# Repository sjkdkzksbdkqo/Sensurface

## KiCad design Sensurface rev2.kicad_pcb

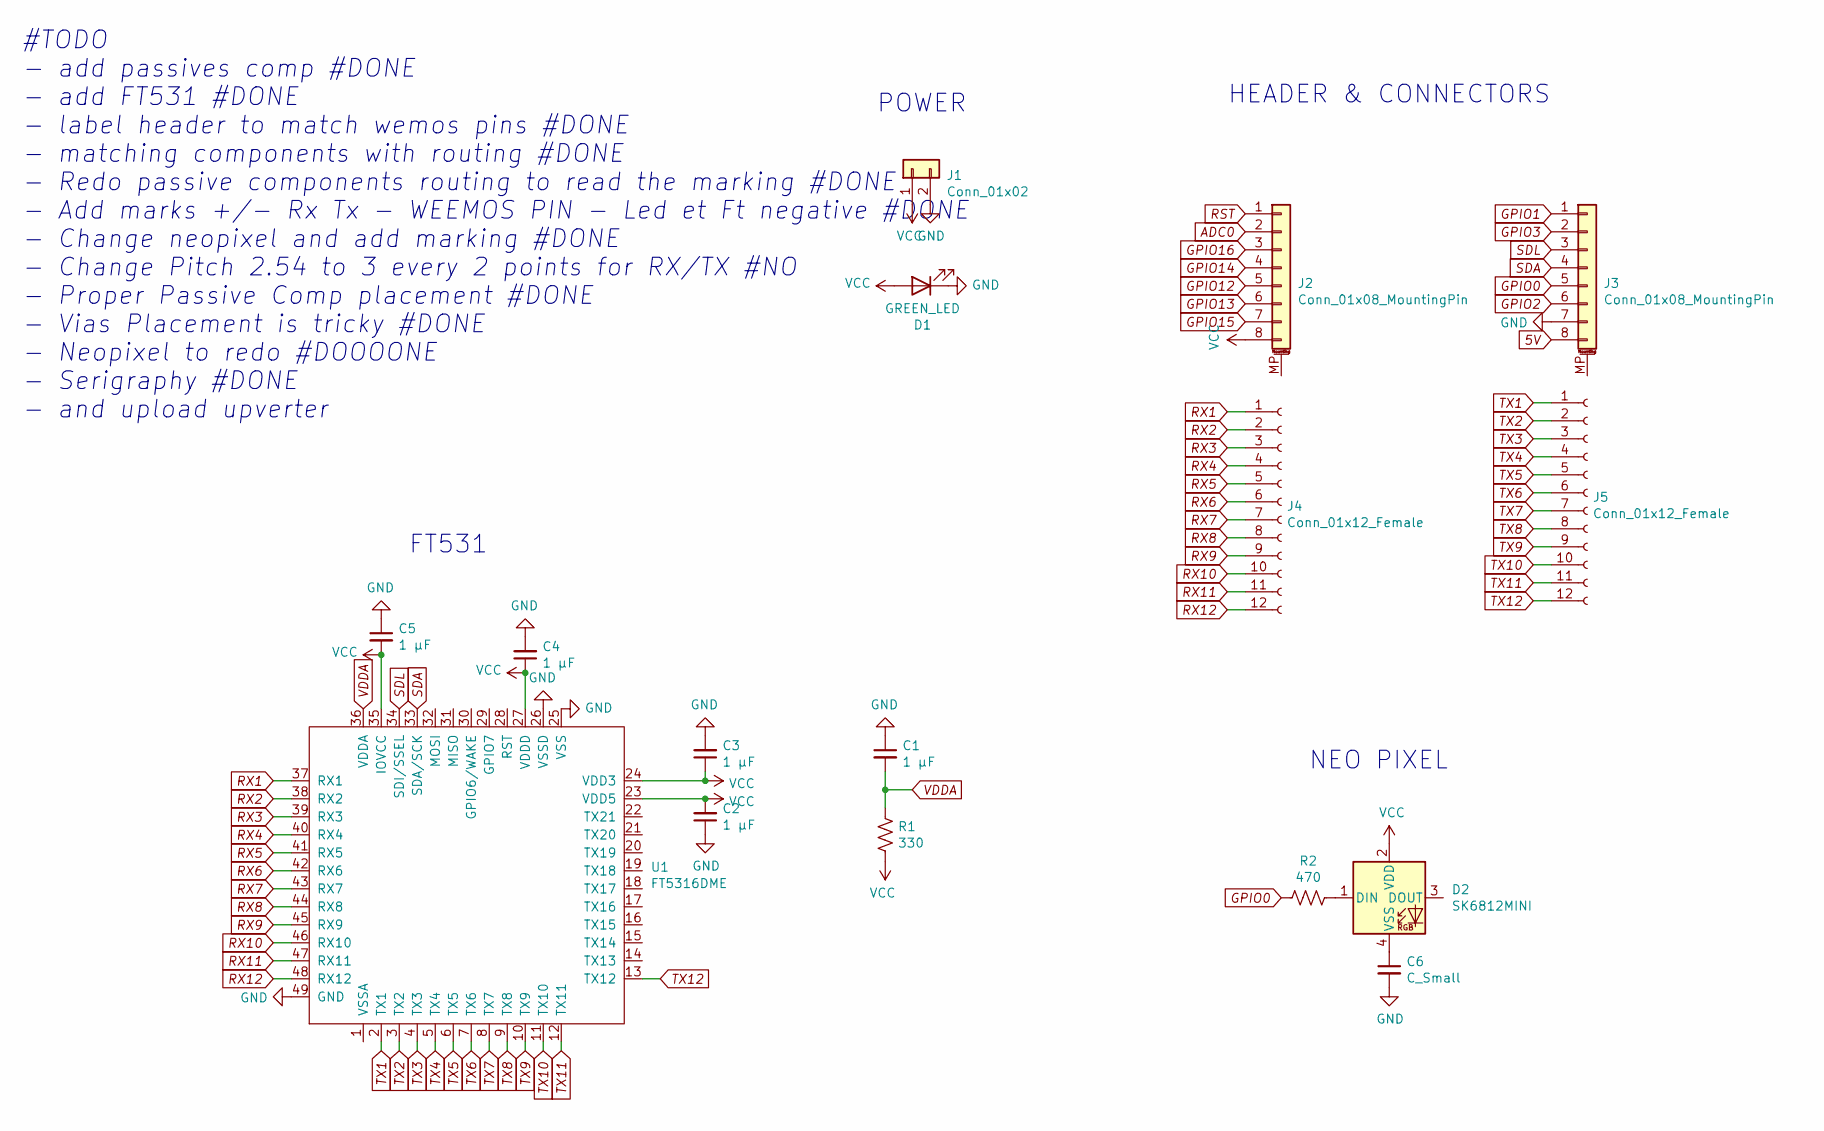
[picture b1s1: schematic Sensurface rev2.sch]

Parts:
C1, C2, C3, C4, C5: 1 µF; C_0603_1608Metric
C6: C_Small; C_0603_1608Metric
D1: GREEN_LED; LED_0805_2012Metric
D2: SK6812MINI; LED_SK6812MINI_PLCC4_3.5x3.5mm_P1.75mm
J1: Conn_01x02; JST_EH_S2B-EH_1x02_P2.50mm_Horizontal
J2, J3: Conn_01x08_MountingPin; PinHeader_1x08_P2.54mm_Vertical
J4, J5: Conn_01x12_Female; TerminalBlock_Phoenix_MPT-0,5-12-2.54_1x12_P2.54mm_Horizont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
R1: 330; R_0603_1608Metric
R2: 470; R_0603_1608Metric
U1: FT5316DME; QFN-48-1EP_6x6mm_P0.4mm_EP4.2x4.2mm

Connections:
5V: J3.8
ADC0: J2.2
GND: C1.1, C2.1, C3.2, C4.2, C5.1, C6.2, D1.1 (K), J1.2, J3.7, U1.25 (VSS), U1.26 (VSSD), U1.49 (GND)
GPIO0: J3.5, R2.2
GPIO1: J3.1
GPIO2: J3.6
GPIO3: J3.2
GPIO12: J2.5
GPIO13: J2.6
GPIO14: J2.4
GPIO15: J2.7
GPIO16: J2.3
unnamed: C6.1, D2.4 (VSS)
unnamed: D2.1 (DIN), R2.1
RST: J2.1
RX1: J4.1, U1.37 (RX1)
RX2: J4.2, U1.38 (RX2)
RX3: J4.3, U1.39 (RX3)
RX4: J4.4, U1.40 (RX4)
RX5: J4.5, U1.41 (RX5)
RX6: J4.6, U1.42 (RX6)
RX7: J4.7, U1.43 (RX7)
RX8: J4.8, U1.44 (RX8)
RX9: J4.9, U1.45 (RX9)
RX10: J4.10, U1.46 (RX10)
RX11: J4.11, U1.47 (RX11)
RX12: J4.12, U1.48 (RX12)
SDA: J3.4, U1.33 (SDA/SCK)
SDL: J3.3, U1.34 (SDI/SSEL)
TX1: J5.1, U1.2 (TX1)
TX2: J5.2, U1.3 (TX2)
TX3: J5.3, U1.4 (TX3)
TX4: J5.4, U1.5 (TX4)
TX5: J5.5, U1.6 (TX5)
TX6: J5.6, U1.7 (TX6)
TX7: J5.7, U1.8 (TX7)
TX8: J5.8, U1.9 (TX8)
TX9: J5.9, U1.10 (TX9)
TX10: J5.10, U1.11 (TX10)
TX11: J5.11, U1.12 (TX11)
TX12: J5.12, U1.13 (TX12)
VCC: C2.2, C3.1, C4.1, C5.2, D1.2 (A), D2.2 (VDD), J1.1, J2.8, R1.2, U1.23 (VDD5), U1.24 (VDD3), U1.27 (VDDD), U1.35 (IOVCC)
VDDA: C1.2, R1.1, U1.36 (VDDA)

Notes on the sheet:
FT531
POWER
HEADER & CONNECTORS
NEO PIXEL
#TODO - add passives comp #DONE - add FT531 #DONE - label header to match wemos pins #DONE - matching components with routing #DONE - Redo passive components routing to read the marking #DONE - Add marks +/- Rx Tx - WEEMOS PIN - Led et Ft negative #DONE - Change neopixel and add marking #DONE - Cha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

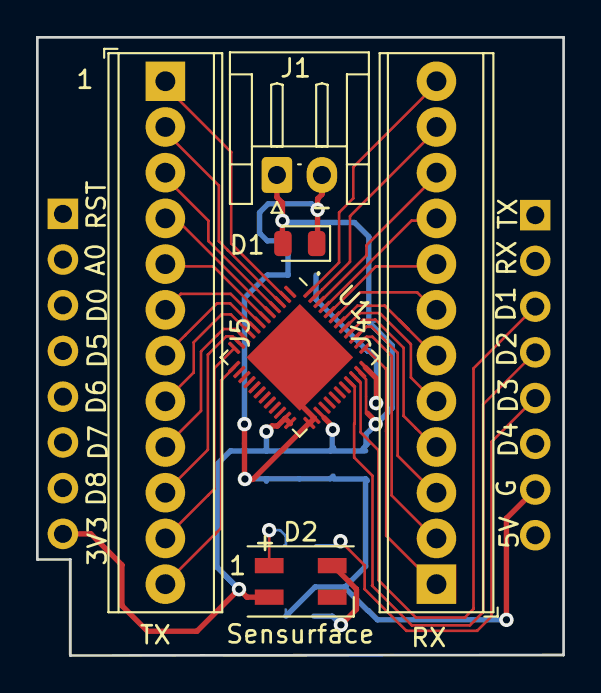
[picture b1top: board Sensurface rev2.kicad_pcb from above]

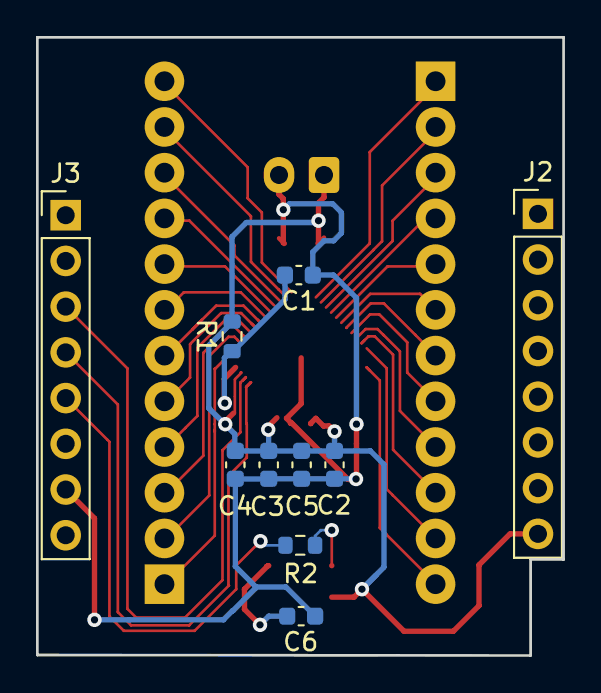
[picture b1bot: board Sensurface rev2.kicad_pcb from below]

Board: 2 copper layers, 29.2 x 34.3 mm, 16 parts (10 on the bottom side), 32 nets.
